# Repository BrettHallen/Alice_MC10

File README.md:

# Purpose
Simple designs for the Tandy TRS-80 MC-10 and Matra Alice.<br>

This boldly red computer is a French version of the Tandy MC-10 using the same Motorola 6803 CPU clocked at 890KHz and using the same MC6847 Video Display Generator (VDG).<br>

It was built by French companies Matra and Hachette but seems to be commonly known simply as the "Matra Alice".<br>

## YouTube Videos
- [Part 1: First Look](https://youtu.be/JoOMIVsprkE)
- [Part 2: Keyboard Problem](https://youtu.be/W2BdekgW1rA)
- [Part 3: Tandy TRS-80 MC-10 Comparison](https://youtu.be/A9SVZOl3z24)
- [Part 4: Keyboard Fixed & Internal 8KB RAM Upgrade](https://youtu.be/OvdkhOnV7no)

## RGB Video Pinout
- Pin 1 = n/c
- Pin 2 = ground
- Pin 3 = red
- Pin 4 = synch
- Pin 5 = green
- Pin 6 = audio
- Pin 7 = blue

I had to tweak variable resistor R45 in the video output stage to get a stable image.<br>

It appears to adjust the level of Field Sync. and Horizontal Sync. signals coming out of the MC6487 VDG.<br>

## [DIN-to-VGA Adapator](/DIN_To_VGA)
A simple adaptor board to take the 7-pin DIN output (via a 7-pin DIN male-to-male cable) and convert to a VGA socket & 3.5mm audio socket.<br>

## [Internal 4KB-to-8KB RAM Upgrade](/Internal_8KB_RAM)
Upgrade the Alice or MC-10 internal RAM from 4KB to 8KB.  Note that the extra 4KB isn't available if the 16KB expansion is also attached.<br>

BUT ... check out the expander below as there is a version that should work with the 8KB upgrade.<br>

## [RGB Video Modification](/RGB_Video) (Work In Progress)
Convert the MC-10 video output from RF modulated to RGB - design is based on the Matra Alice.<br>

## [Expander](https://github.com/Fred72z/ALICE)
Check out [Fred72z's](https://github.com/Fred72z) excellent expansion for Alice & MC10 ... RAM, joysticks, cartridge.

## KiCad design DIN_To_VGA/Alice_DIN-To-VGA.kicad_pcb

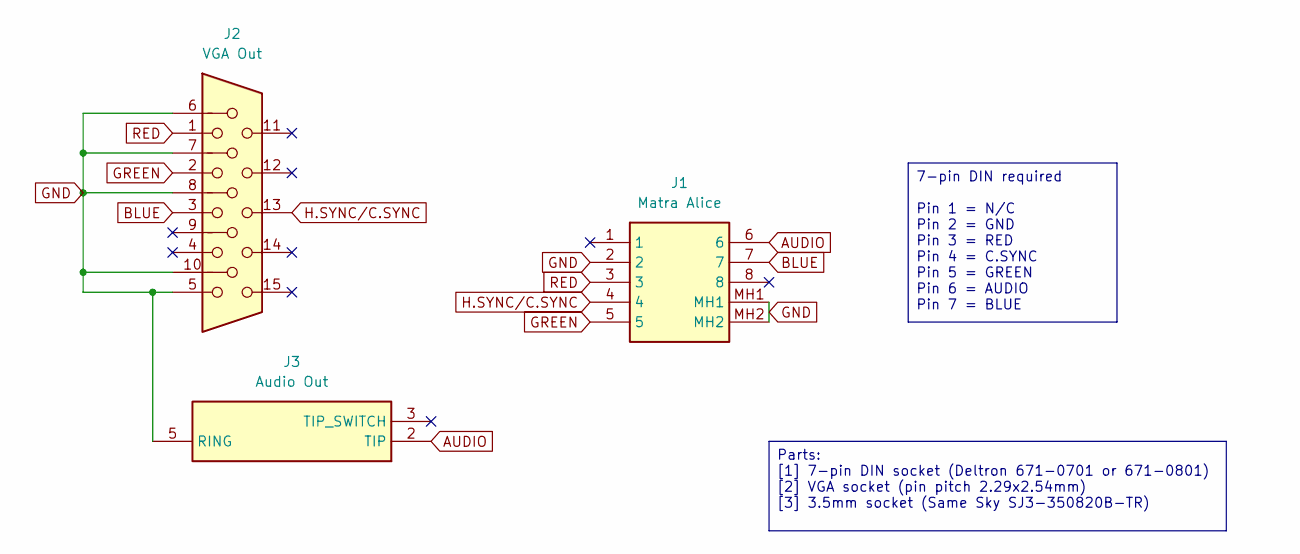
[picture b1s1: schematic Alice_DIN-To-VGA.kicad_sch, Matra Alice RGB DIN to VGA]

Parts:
J1: Matra Alice; 6710801; Manufacturer_Part_Number 671-0801
J2: VGA Out; DSUB-15-HD_Socket_Horizontal_P2.29x2.54mm_EdgePinOffset8.35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
J3: Audio Out; SJ3350820BTR; Mouser Part Number 179-SJ3-350820B-TR

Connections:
AUDIO: J1.6, J3.2 (TIP)
BLUE: J1.7, J2.3
GND: J1.2, J1.MH1, J1.MH2, J2.5, J2.6, J2.7, J2.8, J2.10, J3.5 (RING)
GREEN: J1.5, J2.2
H.SYNC/C.SYNC: J1.4, J2.13
RED: J1.3, J2.1
V.SYNC: J2.14

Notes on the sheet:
Parts: [1] 7-pin DIN socket (Deltron 671-0701 or 671-0801) [2] VGA socket (pin pitch 2.29x2.54mm) [3] 3.5mm socket (Same Sky SJ3-350820B-TR)
7-pin DIN required Pin 1 = N/C Pin 2 = GND Pin 3 = RED Pin 4 = C.SYNC Pin 5 = GREEN Pin 6 = AUDIO Pin 7 = BLUE

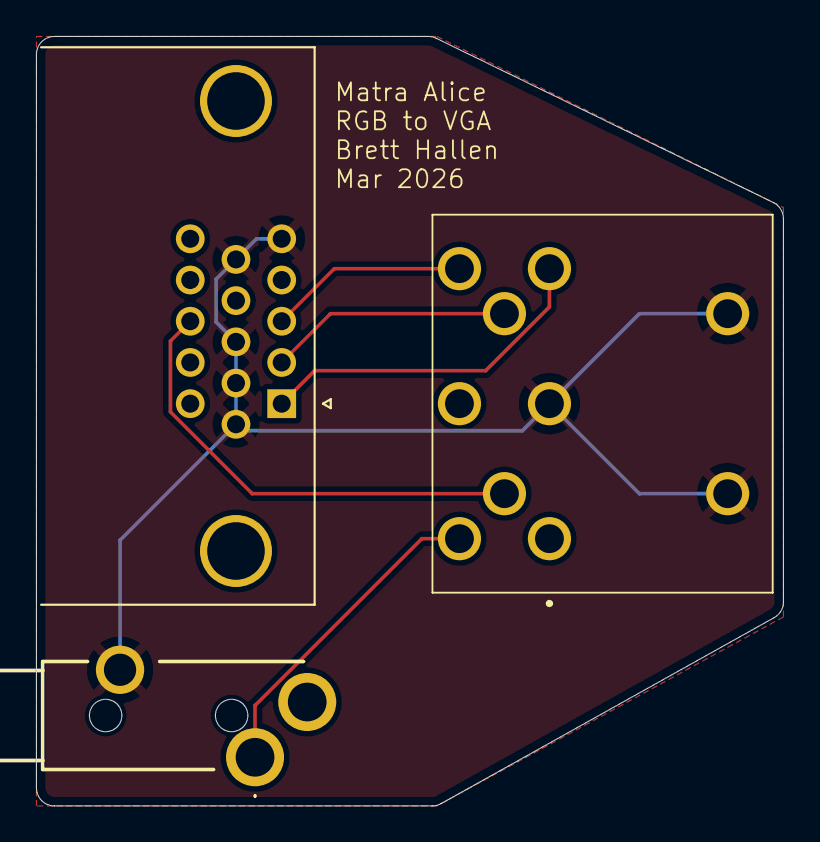
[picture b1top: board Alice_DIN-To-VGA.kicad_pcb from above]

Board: 2 copper layers, 41.5 x 42.8 mm, 3 parts (0 on the bottom side), 6 nets.

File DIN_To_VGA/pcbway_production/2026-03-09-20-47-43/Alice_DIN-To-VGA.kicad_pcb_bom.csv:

Designator,Quantity,Value,Footprint,Package,MPN,DNP,Mount_Type,Description,Height,Manufacturer_Name,Mouser Part Number,Mouser Price/Stock
J1,1,Matra Alice,6710801,,671-0801,,tht,"Deltron 8 Pole Right Angle Din Socket Socket, 2A, 100 V ac, Lockable",19.5,DELTRON COMPONENTS,,
J2,1,VGA Out,DSUB-15-HD_Socket_Horizontal_P2.29x2.54mm_EdgePinOffset8.35mm_Housed_MountingHolesOffset10.89mm,,,,tht,"15-pin D-SUB connector, socket (female), High density (3 columns), Triple Row, Generic, VGA-connector",,,,
J3,1,Audio Out,SJ3350820BTR,,SJ3-350820B-TR,,tht,"3.5 mm Stereo Jack, Through Hole, 2 Conductors, 1 Internal Switches,  Tape & Reel Packaging",5.3,Same Sky,179-SJ3-350820B-TR,https://www.mouser.co.uk/ProductDetail/Same-Sky/SJ3-350820B-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
